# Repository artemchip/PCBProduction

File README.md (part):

## Домашняя фабрика прототипов печатных плат
Методов изготовления печатных плат очень много: сперва было ручное выцарапывание дорожек ножом, потом лак, потом лазерные принтеры и ЛУТ, потом фоторезист, и сейчас ЧПУ станки и фрезеровка дорожек.
Все методы делятся на травление и фрезеровку. Последняя недостаточна точна. Поэтому остановимся на первом. И в промышленности используется фоторезистивная его разновидность, а это явно не спроста.
Я расскажу как воспроизвести эти процессы в домашних условиях с точностью дорожка/зазор 0.1-0.15 мм, отверстие 0.2-0.3 мм, поясок 0.15 мм.

Да, на YouTube по запросу "изготовление печатных плат в домашних условиях" вы найдете много видео. Но мало где демонстрируется процесс металлизации отверстий, позволяющий изготавливать двухслойные платы. Да и все остальное там показывается плохо, недостаточно подробно, не учитываются нюансы и точные параметры процесса необходимые для достижения вышеуказанной околопромышленной точности и качества. Также там демонстрируются только удачные дубли, а весь брак, которого там 90% остается за кадром.

А что можно сказать про компании, которые занимаются изготовлением печатных плат на заказ, под ключ, профессионально? Если их спросить как они это успешно делают - то они ответят, что используют процесс, разработанный компанией X. А компания X предоставит вам базовую информацию, список этапов, но о тонкостях и параметрах каждого ничего не скажет, а лишь предложит за несколько миллионов рублей купить их оборудование которое делает каждый этап идеально. И даже если вы купите - вы не узнаете точный состав используемых растворов и иные параметры и будете зависеть от поставок этих растворов и иных материалов компанией X, ежегодно оплачивать дорогие лицензии их программного обеспечения, не говоря уже о том что оборудование рассчитано под большие панели и объемы и не подходит для прототипирования в плане стоимости и размеров.

Я представляю вам процесс в котором все используемое программное обеспечение разработано мной и имеет открытый исходный код, все используемые материалы доступны для свободного приобретения физическими лицами в малых объемах, все используемые растворы имеют открытый рецепт, точную инструкцию приготовления и каждый из ингредиентов - это не торговое название, а конкретная формула, все оборудование можно купить в любом месте, а не только у одной компании и его чертежи и 3D модели публично доступны.

## Точность

## Методы в фоторезистивной технологии
Ключевым моментом в изготовлении двухслойных плат является химическая металлизация стенок переходных отверстий.
Но их мало металлизировать, нужно их металлизацию защитить от растворения при травлении проводящего рисунка.
Поэтому существуют три метода такой защиты:
1. Тентинг-метод. Металлизацию отверстий защищает непосредственной сам пленочный фоторезист, за счет того что он толстый (50 мкм). Плюс данного метода в том, что он самый простой, легкий и дешевый. Минус - он неточный: дорожка/зазор 0.15 мм, отверстие 0.3 мм, поясок 0.2-0.3 мм. Самое главное - поясок отверстия должен быть большим.
2. Позитивный метод. Наиболее часто применяемый в промышленности. Фоторезист наносится на свободные от дорожек и отверстий участки, затем осаждается гальванический слой меди и поверх него той же гальваникой осаждается слой олова, либо олова-свинца. Плюс - точность выше: дорожка/зазор 0.1 мм, отверстие 0.2 мм, поясок 0.15 мм.
Минус - нужен дополнительный раствор для осаждения олова и удаления его. Также нужны оловяные электроды для его осаждения (которые дорогие). Этот раствор нестабилен, быстро разлагается, да и покрытие олова на медь имеет не очень хорошее сцепление, для решения этих проблем нужны проприетарные реактивы.
3. Полуаддитивный метод с дифференциальным травлением. Используется стеклотекстолит с тонкой медной фольгой (3 мкм). Выполняется осаждение меди на стенках отверстий, за счет чего усиливается и толщина основного слоя до 5 мкм. Фоторезист наносится на свободные от дорожек и отверстий участки, после чего толщина меди непокрытых им дорожках и отверстиях наращивается до 30-40 мкм той же гальваникой. Затем выполняется травление, 5 мкм стравливается быстро, а 40 мкм - не стравливается. Тут точность еще выше и дорожка/зазор может достигать 0.05 мм, но минус в том, что сложно найти на рынке стеклотекстолит FR-4 с такой тонкой фольгой. А брать 18 или 35 мкм и травить до толщины 3 мкм - неравномерно будет и ничего не получится. Стравить всю фольгу и затем с нуля осадить медь - недостаточно хорошо держаться будет.

В общем, надежно, стабильно и повторяемо в домашних условиях работает только первый метод. Он продемонстрирован в видео Demo.mp4 (Demo.zip).

## Тентинг-метод
1. Лист FR-4 и обработка на ЧПУ.
2. Химическое и гальваническое осаждение меди.
3. Нанесение фоторезиста, засветка, проявка.
4. Травление проводящего рисунка.
5. Удаление фоторезиста.
6. Нанесение паяльной маски, засветка, проявка, дубление.
7. Нанесение шелкографии.
8. Депанелизация.
9. Печать паяльной пасты, Pick & Place компонентов, пайка феном.

## Файлы проекта
Вам нужно экспортировать Gerber-файлы из САПР в котором вы разработали свою плату. Также если планируете сборку/пайку SMD нужно экспортировать centroid-файл.
Выбираем эти файлы в моем программном обеспечении, которое лежит в папке Software репозитория. Версия 3 более удобная и простая, версия 2 более расширенная.
С параметрами в главном меню лучше не играться. Если вы хотите панель побольше, чтобы уместить плату размером побольше или большее количество маленьких плат - вам придется переделывать файлы 3D моделей в последующих этапах, не исключены дополнительные проблемы.

## Лист FR-4 и обработка на ЧПУ
Я использую стеклотекстолит FR-4, листы 200x300 мм, толщина от 0.5 до 1.5 мм в зависимости от применения полученной печатной платы, толщина медной фольги от 18 мкм до 35 мкм. Продается много где.
Лучше использовать 18 мкм. Казалось бы, какая разница, 18 мкм или 35 мкм, но когда у вас дорожка/зазор 0.15 мм - разница существенная в боковом подтравливании.

Для обработки я использую ЧПУ станок CNC 3018 MAX с Aliexpress со шпинделем на 500 ватт.
После покупки станка я его доработал аппаратно:
1) добавил пылесборник на шпиндель, к которому подключаю пылесос (тоже продается на Aliexpress)
2) добавил камеру на каретку со шпинделем, 3D модели для печати крепления прилагаю
3) добавил микропереключатели чтобы сделать возможным homing

Важно откалибровать количество шагов на миллиметр у ЧПУ станка по каждой из осей, а также угол между осями XY и иные параметры. Делаю это один раз с помощью собственного программного обеспечения и фотошаблона, размещаемого в поле зрения камеры на рабочем поле станка.

Также нужно подобрать экспериментально скорость подачи и иные параметры.

В качестве подложки (жертвенного стола) я использую толстый (5 мм) лист FR-4 без фольги, на эту подложку уже креплю тонкий рабочий лист стеклотекстолита FR-4. Важно чтобы он ровно (без прогибов) ложился на подложку.
Выглядит и крепится это примерно так:

Я использую сверла фирмы X-CAN (с Ozon) для сверления основных и реперных отверстий и для вырезания квадратной панели фрезу 1.5 мм тоже от них. Выглядят они так:

Важно для сверления всех отверстий использовать сверла одной и той же фирмы из одной и той же серии, одной и той же длины, с одним и тем же хвостовиком чтобы они одинаково зажимались в патрон и сверление отверстий каждого диаметра происходило на одинаковом уровне оси Z и кривизна этой оси не портила позиционирование отверстий по XY. Также важно осторожно устанавливать сверло в патрон, не допуская изгиба, иначе центр вращения не совпадет с центром сверла и диаметр отверстия будет чуть больше.

Саму обработку тоже запускаю из своего программного обеспечения (как это делать показано в видео), важно подключать станок и его камеру в два USB порта (не использовать USB-хаб для объединения их в один), также не использовать USB-удлинители, потому что они могут неожиданно во время сверления оборвать соединение. Ранее я использовал Grbl Control, но там нет функционала повтора цикла, отметки какие отверстия просверлены, какие нет, превью, компенсация кривизны, т.е. функционал общий, не такой гибкий и заточенный под производство печатных плат, как в моем ПО.

Далее нужно снять заготовку с ЧПУ станка, обработать поверхность и края наждачкой зернистости от P400 до P800 (лучше последнее), не пропуская области вокруг отверстий (чтобы они тоже покрывались царапинами от зерен наждачки), проткнуть иголкой или сверлом каждое отверстие в котором застряла стружка, затем протереть безворсовой салфеткой, смоченной в изопропаноле и просушить 10 минут при 70C в конвекционной печи (пойдет обычная кулинарная, не микроволновая, а та что на ТЭНах).
Далее заготовку нужно взвесить, желательно с точностью до миллиграммов, чтобы в дальнейшем по плотности меди оценивать толщину фольги (но это необязательно).

При промывке изопропанолом необходимо использовать безворсовые салфетки (cleanroom wipers):

Вот так заготовка выглядит после этого этапа:

У меня заготовка около 122x122 мм, но вы можете в настройках программы попробовать установить другой размер, но вам придется и последующие этапы и станки под него адаптировать, и возможно вы наступите на грабли.
Не обязательно использовать CNC 3018 MAX, может подойти и другой ЧПУ станок. Но ручной микродрелью сверлить точно не стоит - отверстия будут неаккуратными и непригодными к следующему этапу. Да и в проводящий рисунок они не попадут. Даже с ЧПУ станком, но не откалиброванным не попадут, а вручную сверлить - шансов вообще нет. На YouTube у некоторых людей получается - но это везение и удачные попытки, повторяемость низкая, а неудачи остаются за кадром, да и неудобно это.

После этого этапа для перемещения заготовки нужно брать её за торцы (не за поверхность/середину). А если хочется положить заготовку, не делайте этого, ставьте вертикально на подставку.

От этого этапа до следующего можно её держать долго (хоть неделю).

В папке CNC лежат файлы настроек ПО под мой станок (они вам не сильно понадобятся, потому что у вас будут другие результаты калибровки), а также 3D модели (из Blender) деталей для печати из PETG пластика (адаптер для пылесборника, крепление для камеры, подставка и адаптер для депанелизации [о ней позже]).

Время этапа: около 30 минут.
Стоимость оборудования: $400.
Стоимость одного цикла: $1.5 (стоимость FR-4 + износ сверел и фрез).

## Химическое и гальваническое осаждение меди
Это очень важный этап в изготовлении двуслойных плат, поскольку соединяет два слоя путем осаждения меди на стенках отверстий. Не забываем про средства индивидуальной защиты от опасных веществ и о том, что подэтапы этой операции важно выполнять друг за другом и без пауз. Под паузой понимается перерыв дольше минуты-двух.
Моя установка выглядит так:

Что мы видим: рама, шаговый двигатель, ходовой винт и ездящий по одной оси стол. Это все взято и собрано из еще одного набора для сборки CNC 3018 (взял вариант на Ozon без шпинделя и лазера) и получил такой набор.
Этот стол движется туда-сюда для перемешивания всех ванн сразу. В моей программе можно нажать кнопку которая отправит необходимые для такого движения GCode команды, а можно сохранить их как файл. Также можно с его помощью сгенерировать файл GCode, залить на SD-карту и через автономный контроллер запускать его на этом станке, что я и делаю.

Перемешивать нужно именно в направлении которое показано на фото, т.е. поперек ванн, чтобы раствор затекал и смачивал отверстия в заготовке.
Не надо делать всякие другие механизмы перемешивания, они затратнее, опробованы мной и работают хуже.
На алюминиевом столе стоит полипропиленовый контейнер купленный в FixPrice. К его дну на "жидкие гвозди" приклеена подставка. В этих подставках стоят сами ванны.
Подставки напечатаны на 3D-принтере из PETG-пластика, файлы моделей прилагаю.

Также на крышке, которая держит заготовку, расположен соленоид. Он нужен чтобы бить в торец заготовки и вышибать из её отверстий диаметром 0.3 мм застрявшие пузырьки выделяющегося в процессе водорода.

Сами ванны напечатаны из чистого полипропилена (PP), конечно в YOUSU PP есть добавки которые снижают усадку и это хорошо, а в REC PP+ они еще лучше.
Полипропилен со стекловолокном (PP-GF) нельзя использовать, хоть он печатается легче, но он дает пористую структуру, у него спекаемость слоев и устойчивость к химии хуже, он будет протекать, спустя месяц раствор выльется из закрытой емкости и оставит налет. Не подойдут и другие 3D-печатные полимеры. Важна именно такая форма ванны, как в моих файлах 3D модели. Квадратная (прямоугольная) форма заставит медь оседать в углах сосуда и усложнит печать такой ванны, а также промывку после её использования.
Пластик PP сложный, необходим 3D принтер с закрытым объемом (пассивная или лучше активная термокамера). Я использовал Creality K1 Max, сопло 0.6 мм (не используйте 0.4 мм и менее, заклинит экструдер так как полипропилен мягкий).
Для обеспечения адгезии к столу необходимо положить лист полипропилена 4 мм (именно лист и именно такой толщины, можно больше, но не меньше). Важно его закрепить к столу зажимами, а лучше болтами.

Печатать нужно медленно 50 мм/сек при температуре 225C и без нагрева стола, с высотой слоя 0.1 мм.
Не печатайте на скотч, на специальные адгезивы и фирменные пленки для полипропилена, у вас ничего не получится, нужен именно лист (и толстый, 4-5 мм).
После печати вырезаем кусок из листа, печатаем подставку из PETG.
Приклеиваем дно ванны к дну подставки и ставим её в общее место. Пойдет любой каучуковый клей, хоть и пишут что для полипропилена он не подходит. А вот эпоксидный клей действительно тут не подходит. Вот так:

Печатаем также крышки из чистого PP, можно их подписать. Эти крышки плотно закрывают ванну обеспечивая герметичность и хранение растворов на месяцы и годы.
Также необходима рабочая крышка из PETG, с продетой в нее медной проволокой и зажимами крокодил, а также соленоидом, которые будут держать заготовку. Вот так:

Да, можно сделать лучше и чтоба она более ровно держала заготовку, но и так работает прекрасно.

Черные ванны у меня из ABS-GF4 с серыми крышками из PETG - они для воды, поэтому из таких простых пластиков.

Все ванны размещены в контейнере из того же полипропилена на всякий случай потому что может разлиться и пусть оно лучше туда выльется чем разольется по всему помещению.
3D печать из полипропилена - это лучший способ изготовить эту установку дома. Склеивание из листов, использование герметиков, других пластиков и методов не работает - герметики и клеи не устойчивы к химии и откажут после месяца работы, если конечно не сразу.
Литье может сработать, но в домашних условиях и единичном экземпляре - это весьма дорого.

В ваннах (справа налево) следующие растворы:
1. Кислая очистка.
2. Промывка 1.
3. Активация.
4. Пост-активация.
5. Промывка 2.
6. Химическое осаждение меди (electroless copper deposition).
7. Промывка 3.
8. Гальваническое осаждение меди (electrolytic copper deposition) (отдельно).

Состав этих растворов описан в Process 01.pdf лежащем тоже в репозитории. Только у меня 500 мл раствора, не как у Hydrogen Time, автора этой работы и соотвественно количество каждого ингредиента пропорционально больше. Главное готовить их на магнитной мешалке, не спешить и подождать подольше когда каждый ингредиент растворится перемешиванием почти полностью или вовсе полностью, перед добавлением следующего.
Для приготовления растворов используем дистилированную воду или даже деионизированную.
А вот для промывки можно фильтрованную питьевую из под крана, хотя лучше тоже дистилированную, особенно для промывки 2.
Раствор кислой очистки и активации условно вечный, живет год-два и больше, как понять, что он истек, написано в Process 01.pdf. Промывки меняю раз в 5-10 циклов производства. Пост-активатор меняю раз в 20-30 циклов. Химическую медь готовлю заново каждый цикл.
У меня кислая очистка, как и гальваническое осаждение меди (о котором позже) происходят при комнатной температуре, в отличии от Process 01.
Также там указано что раствор electroless copper deposition нужно после использования подкислять, и перед следующим использованием наоборот подщелачивать. Но не указано до какого pH, поэтому я просто в каждом производственном цикле готовлю его заново на магнитной мешалке непосредственно перед использованием. Тем более этот раствор склонен осаждать медь на любых пылинках, соринках, неровностях сосуда в который налит. Но если его использовать и после выливать и выбрасывать - проблем нет. Если после использования и слива раствора на его стенках все же осела медь - то желательно перед следующим циклом производства растворить её персульфатом аммония.
В составе electroless copper deposition не уточнено 4 капли Тритон X-100 - это сколько. Я использую 0.1-0.15 мл на 500 мл раствора (отмеряю шприцом).

Также рецепт раствора electrolytic copper deposition у меня другой (живет около 1 цикла производства, если заготовка 122x122 мм и ванна 2л):
750 мл дистилированной воды (горячей, 80C)
180 г медного купороса
130 мл серной кислоты (45% аккумуляторной 1.28 г/см^2)
0,06 г тиомочевины
0,06 г хлорида натрия
0.05-0.1 мл Тритон X-100
Долить воды до отметки в 1 литр

Можно использовать вариант с проприетарным блескообразователем (живет около 4 циклов производства, если заготовка 122x122 мм и ванна 2л):
750 мл дистилированной воды (горячей, 80C)
160 г медного купороса
200 мл серной кислоты (45% аккумуляторной 1.28 г/см^2)
0.07 г хлорида натрия
5 мл Купралайт-7400
Долить воды до отметки в 1 литр

Есть еще рецепт от канала "шоу бородатого инженера" (не проверял, не знаю насколько хорошо работает):
750 мл дистилированной воды (горячей, 80C)
250 г медного купороса
200 г серной кислоты (45% аккумуляторной 1.28 г/см^2)
5 мг тиомочевины
2,7-нафталиндисульфокислота 0.5г/л
Возможно несколько капель Тритон X-100 или иного ПАВ
Долить воды до отметки в 1 литр

После истечения "срока жизни" покрытие неравномерное. Вы можете следить за истечением его срока службы по уровню мутности раствора, он возрастет когда срок начнет подходить к концу.

Этот раствор заливается вот в такую ванну из полипропиленового контейнера (3D модели тоже прилагаю). Тут шаговый двигатель, который перемешивает раствор покачиванием заготовки на 5-10 мм по нижнему краю.
Вот как это выглядит:

Электроды - это шины из меди М1 размером 3 х 30 х 200 мм, обернутые в полипропиленовую химостойкую ткань (анодные чехлы), для защиты от образования шлама. Конечно лучше медь с добавлением фосфора, но у меня без.
Они должны иметь именно такой размер и площадь и располагаться по обе стороны заготовки, иначе покрытие будет неравномерным. Суммарная площадь анодов должна быть вдвое больше площади заготовки. И они должны для большей равномерности быть подальше от неё. Они будут растворяться в процессе работы, аноды такого размера растворятся наполовину лишь после 100 циклов производства, после их нужно заменить. Каждые 5 циклов производства необходимо отмывать аноды от шлама (промывать чехол водой и обрабатывать сам медный анод наждачкой).

В Process 01 также указан порядок действий для тентинг-метода: clean, water rinse, activate, post activate, water rinse, electroless copper, water rinse, electrolytic copper, water rinse.
Но у меня время другое: clean - 10 минут, activate - 10 минут, post-activate - 5 минут, electroless copper - 1 час, electrolytic copper - 1 час 10 минут.
"Water rinse" в Process 01 - это я просто опускаю заготовку (вместе с крышкой на которой она закреплена) в ванну промывки, на время от 2 до 5 секунд.

Если в растворе активатора плавают хлопья - нужно их отфильтровать, если не помогло - значит истек его срок годности и нужно его приготовить заново.

Итак, выполняем микротравление в горячем (60C) 20% растворе персульфата аммония 10-20 секунд (ну или не очень микро если у нас 35 мкм FR-4, чтобы оставить 18 мкм, 2-3 минуты), затем промываем водой, затем обрабатываем в 5% растворе гидроксида натрия (2 минуты), промываем водой, далее поочередно опускаем заготовку в каждую из ванн системы на нужное время.
Поправка: в видео показана обработка в растворе гидроксида натрия, но вместо этого нужно обрабатывать в 20% растворе лимонной кислоты, как показал опыт после съемки видео.

После химического осаждения меди (electroless copper deposition) проверьте края (торцы) заготовки, если они полностью покрыты медью - подэтап удался, если нет - промойте заготовку водой, повторите активацию, пост-активацию, промывку и выполните химическое осаждение заново в новом растворе химической меди. Если и это не помогло, приготовьте заново растворы активатора и пост-активатора.

Если все нормально - то промываем водой (аккуратно, погружением, можно двойным, чтобы отмыть полностью) и в последнюю ванну [electrolytic copper deposition] погружаем с постоянным током около 2 А на заготовку 122x122 мм (если у вас больше/меньше - пересчитайте пропорционально), заготовка к минусу, аноды к плюсу. Раствор я держу при комнатной температуре, не нагревая его до 60C как Hydrogen Time. Важно как можно больше соединений проводов с заготовкой и анодами сделать паянными, чтобы не болтались.

Если после этого процесса появляются сильные неровности, наросты и большие кристаллы меди, а также сильные заусенцы на углах - значит сила тока слишком большая или электролит грязный, нужно готовить раствор заново и повторять все сначала.

Если все получилось равномерно - промываем водой (хоть из под крана), сушим в печи при 70C около 10 минут и обрабатываем наждачкой Р800, промывая изопропанолом и протирая безворсовыми салфетками. Ставим заготовку на подставку. И так она может дожидаться следующего этапа до нескольких часов точно. Но при дальнейшем её перемещении берите её пальцами за торцы и технологические поля, а вообще в идеале еще и в перчатках.

Результат:

Вы можете взвешивать заготовку до, во время и после процесса, чтобы по массе через плотность меди вычислить толщину (сколько осадили). Только взвешивайте предварительно просушив.

Если вы оставляете этот раствор [electrolytic copper deposition] стоять более 10 минут в ванне без тока и перемешивания - вынимайте из неё аноды и заготовку.

Не используйте всякие графитовые спреи/углеродные краски которые советуют для создания проводимости перед гальваникой самоделкины, это ненадежно. Также ненадежно использование термореактивных веществ типа аммиачного комплекса гипофосфита меди. Если даже оно будет работать устойчиво - то большие (3-5 мм) отверстия непрокроются, и стенки будут не всегда ровные, и еще большой вопрос не сломается ли такая плата в процессе эксплуатации.

Не используйте механическую металлизацию (гильзование), она трудоемка и не выдерживает процесс reflow soldering, да и размеры via там большие.

В папке Galvo есть blend-файл с 3D моделями всего вышеупомянутого.

Время этапа: чуть меньше 2 часов.
Стоимость оборудования: $500 (реактивы, пластик для ванн, механизмы перемешивания, лабораторная посуда, установки вакуумной фильтрации, медные аноды).
Стоимость одного цикла: $0.1 (в случае с электролитом на основе Купралайт-7400), $2 (в случае с моим рецептом).

## Фоторезист: нанесение, засветка, проявка
Ну во-первых: он бывает пленочный и жидкий.
Жидкий редко где встретишь, аэрозольные балоны Kontakt Chemie Positiv 20 и Cramolin Positiv Resist дорогие и мало где продаются, также есть жидкий в банках, содержимое их нужно растворять в этилацетате и распылять с помощью аэрографа.
Ну, во-первых вы не сможете руками распылять одинаково толстый слой при каждом цикле производства, а от толщины зависит энергия экспонирования (сколько света должно попасть). Если конечно не закрепите аэрозольный баллон на каретке ЧПУ станка, который впоследствии испачкается этой жидкостью. Помимо этого, жидкий воняет, к нему прилипает пыль, его нужно 15 минут сушить в конвекционной печи. Да и он как правило позитивный, т.е. те участки куда попал свет растворяются. Это значит что при травлении придется держать свет выключенным, об этом позже.
Да и полезных свойств у жидкого фоторезиста нет: он неспособен как пленка, закрывать собой (образовывать крышки) на отверстиях - следовательно не годится для тентинг метода, а еще не все марки и модели устойчивы в кислых гальванических ваннах, что делает его непригодным для двух оставшихся методов. Да также он слишком тонкий для них. Пригоден он только для однослойных плат.

Промышленность использует пленочный. Я использую Laminar E7715 и Aqua Mer ME720 толщиной 38 мкм. Вы можете использовать любой толщиной от 30 до 50 мкм, годящийся согласно datasheet для тентинг метода. Главное покупайте его у надежного поставщика, храните в темноте, убеждайтесь при покупке, что светозащитная упаковка не вскрыта и на пленке не должно быть царапин, ляпов, полос, волн, ряби и иных дефектов:  
  
Вы их можете даже после проявки не увидеть, а вот при травлении они вам все испортят из-за недостаточной адгезии в этих местах.

Перед нанесением фоторезиста очень важно подготовить поверхность. Да, грубые техпроцессы могут и без такового получится, но если дорожка/зазор 0.1-0.15 мм - это обязательно.
Для этого нужно (обязательно):
1. Обработать наждачкой P600-P800, промыть изопропанолом и протереть безворсовыми салфетками.
2. Микротравление (10-20 секунд в холодном (15C) 20% растворе персульфата аммония), промыть водой.
3. Обработать в 3-5% растворе гидроксида натрия (нет, в 20% растворе лимонной кислоты как показал опыт полученный после съемки видео) в течение 2-5 минут, промыть водой.
Вот как будет если обработать гидроксидом натрия:
    
А вот как если в лимонной кислоте (на дефекты маски внимания не обращать, не нашел качественного поставщика):
    
4. Просушить в печи при 80C 5-10 минут до полной сухости. Вы можете за неиспользуемые технологические поля с краев потрогать заготовку - она должна на ощупь "скрипеть", быть такой же как посуда после тщательного мытья.
5. Проверить рисунок (экспортировать его из моей программы кнопкой "сохранить" в разделе "засветка фоторезиста" и сравнить с тем, что показывает ваш САПР). Экспортированные из Autodesk EAGLE изредка она воспринимает не так. В случае отличий, в их местах удалить дорожку и создать её заново, пере-экспортировать и снова сравнить, и так пока отличия не исчезнут.

Итак, выключаем свет. Чтобы что-то видеть нужно использовать красный или желтый осветительной прибор (это должен именно светодиод этих конкретных цветов, монохроматический, одной длины волны, около 600 нм, не RGB [выше 550 нм фоторезист не чувствителен]).
Достаем рулон, отрезаем нужный кусок. Отрезать квадрат на 1 см больше заготовки (или меньше, см. примечание ниже). Отрезаем 2 штуки (на каждую из сторон). Я использую для этого резак для бумаги, но вы можете и ножницами:

Важно убедиться, что на поверхности фоторезиста нет ряби, в противном случае это брак или у него истек срок годности (бывает, что и такое продают).

Берем лист бумаги A4. Сгибаем пополам, раскрываем, кладем рядом со входом ламинатора, сгибом к нему. С куска фоторезиста снимаем защитную пленку (на более шероховатой стороне), с помощью куска скотча или двух кусков скотча.
Эта пленка должна отдираться плавно (не рывками). Кладем на лист бумаги лист фоторезиста, затем заготовку (остывшую хотя бы до 30C после сушки), затем лист фоторезиста (липкой/шероховатой стороной с которой сняли пленку к заготовке). Посмотрите на мои движения в видео и точно повторяйте их. С другой стороны заготовки тоже самое.
Ну а если не можете лучше возьмите рулонный ламинатор который подороже.
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
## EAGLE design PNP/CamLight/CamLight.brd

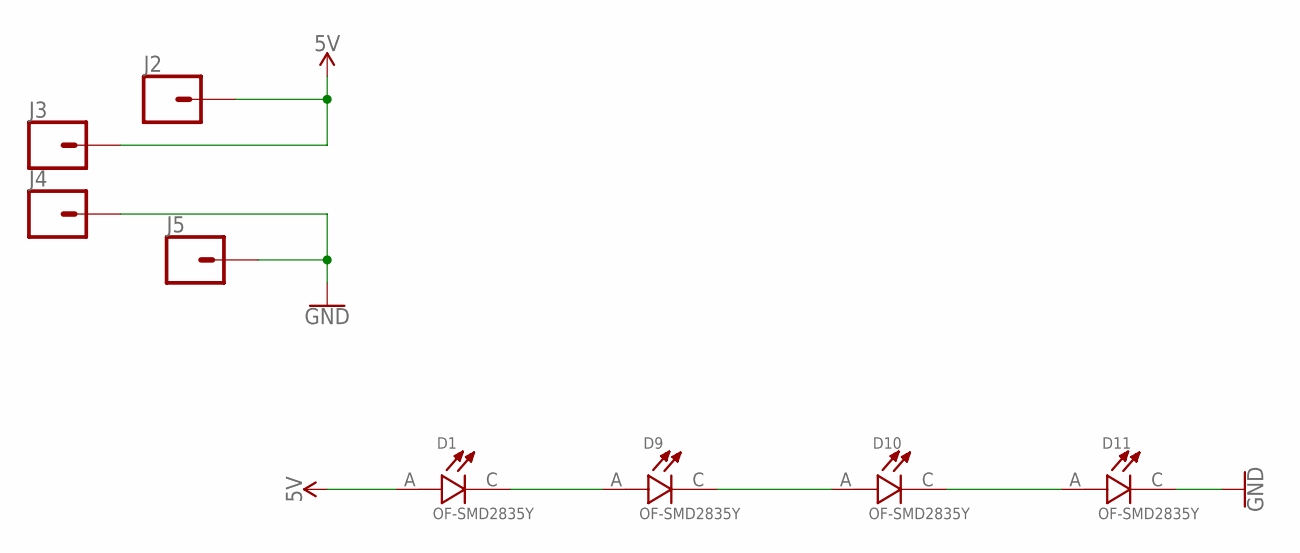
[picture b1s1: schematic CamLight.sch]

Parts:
D1, D9, D10, D11: OF-SMD2835Y; LED_OF-SMD2835Y
J2, J3, J4, J5: CONN_01; 1X01

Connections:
5V: D1.A, J2.1, J3.1
GND: D11.C, J4.1, J5.1
unnamed: D10.C, D11.A
unnamed: D9.C, D10.A
unnamed: D1.C, D9.A

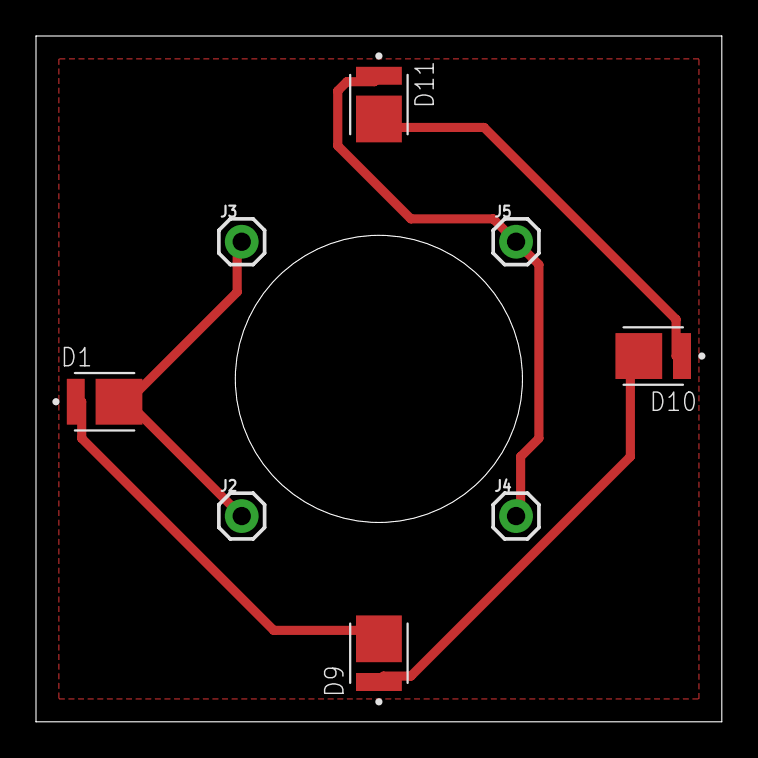
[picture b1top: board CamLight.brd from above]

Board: 2 copper layers, 38.1 x 38.1 mm, 8 parts (0 on the bottom side), 5 nets.

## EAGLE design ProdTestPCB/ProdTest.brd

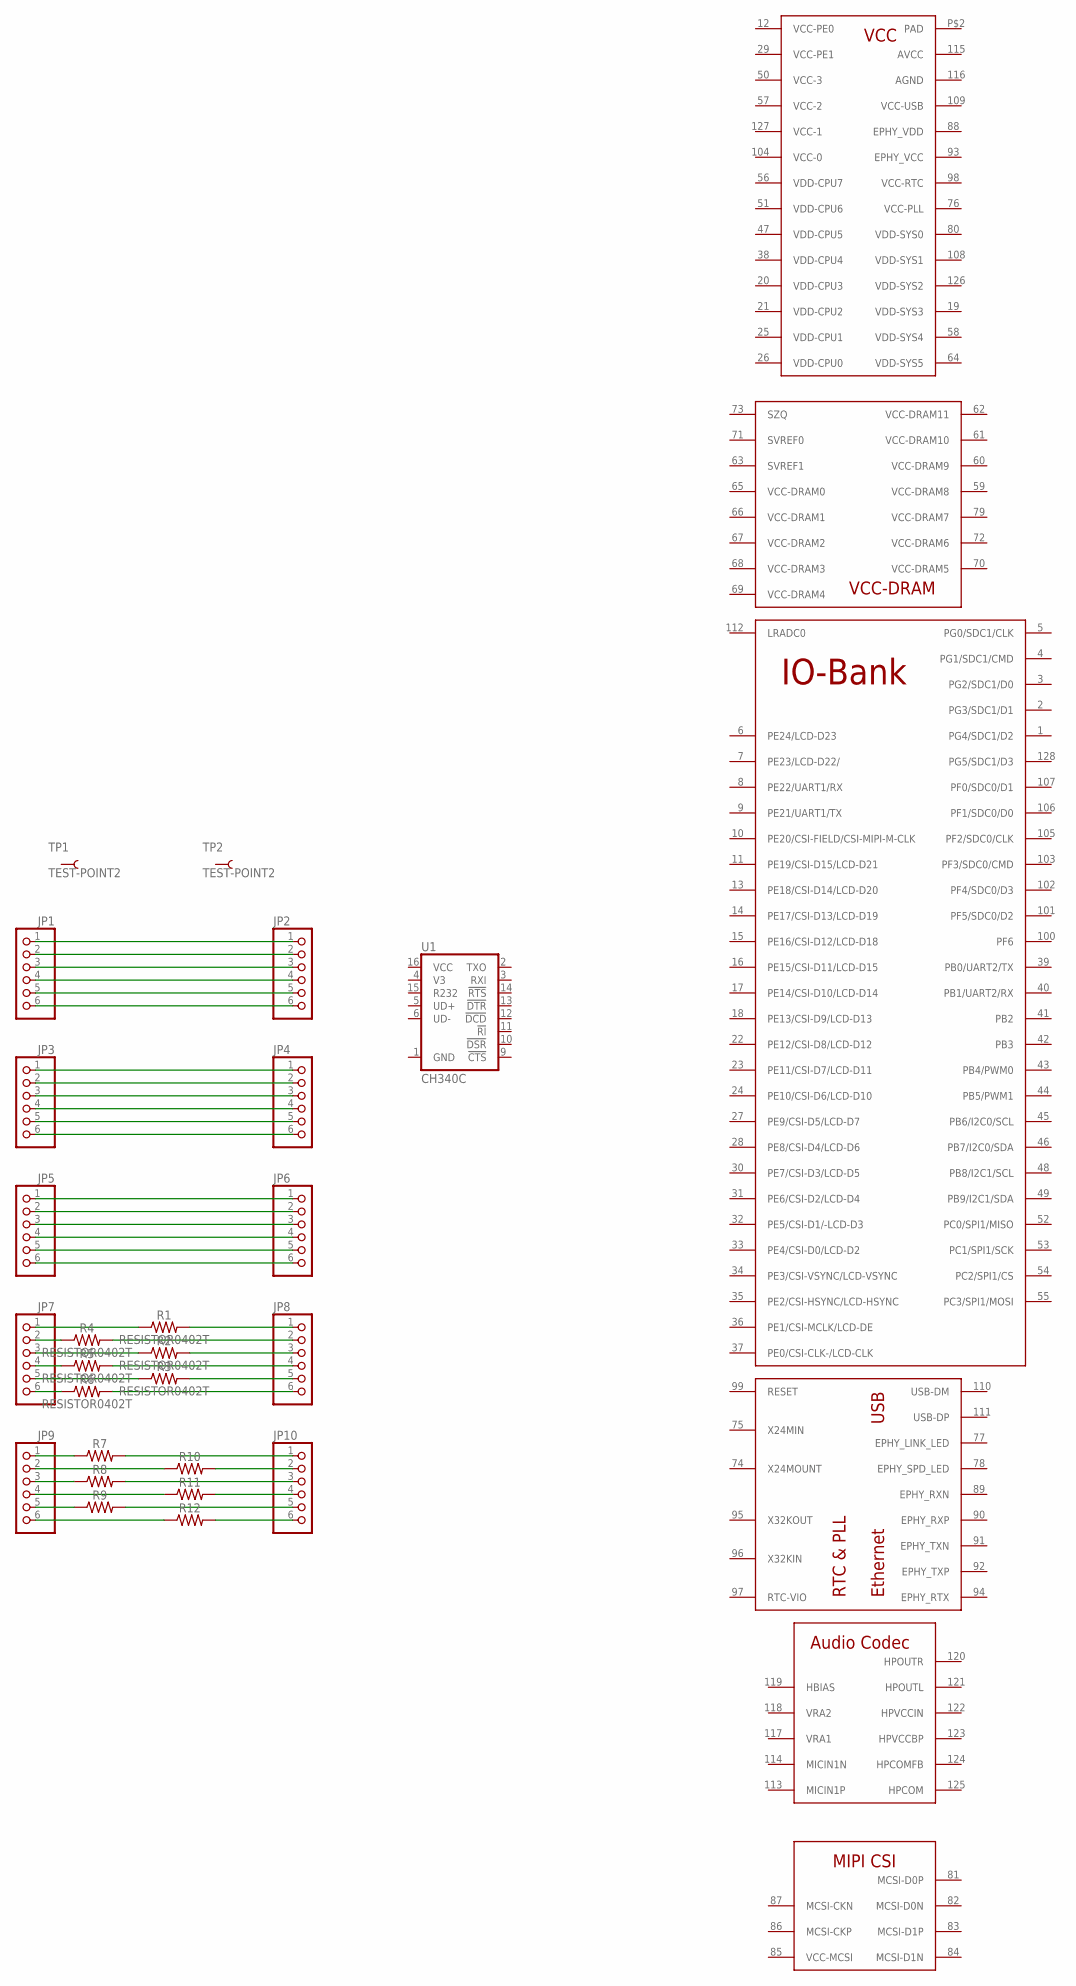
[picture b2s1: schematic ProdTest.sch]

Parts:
JP1, JP2, JP3, JP4, JP5, JP6, JP7, JP8, JP9, JP10: PINHD-1X6; 1X06
R1, R2, R3, R4, R5, R6: RESISTOR0402T; 0402-TIGHT
R7, R8, R9, R10, R11, R12: 0603
TP1, TP2: TEST-POINT2; PAD.02X.02
U1: CH340C; SO016
U$1: V3S; QFP-128

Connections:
unnamed: JP1.1, JP2.1
unnamed: JP1.2, JP2.2
unnamed: JP1.3, JP2.3
unnamed: JP1.4, JP2.4
unnamed: JP1.5, JP2.5
unnamed: JP1.6, JP2.6
unnamed: JP3.1, JP4.1
unnamed: JP3.2, JP4.2
unnamed: JP3.3, JP4.3
unnamed: JP3.4, JP4.4
unnamed: JP3.5, JP4.5
unnamed: JP3.6, JP4.6
unnamed: JP5.1, JP6.1
unnamed: JP5.2, JP6.2
unnamed: JP5.3, JP6.3
unnamed: JP5.4, JP6.4
unnamed: JP5.5, JP6.5
unnamed: JP5.6, JP6.6
unnamed: JP9.1, R7.1
unnamed: JP9.2, R10.1
unnamed: JP9.3, R8.1
unnamed: JP9.4, R11.1
unnamed: JP9.5, R9.1
unnamed: JP9.6, R12.1
unnamed: JP10.5, R9.2
unnamed: JP10.6, R12.2
unnamed: JP10.4, R11.2
unnamed: JP10.2, R10.2
unnamed: JP10.1, R7.2
unnamed: JP10.3, R8.2
unnamed: JP7.2, R4.1
unnamed: JP7.4, R5.1
unnamed: JP7.6, R6.1
unnamed: JP7.5, R3.1
unnamed: JP7.3, R2.1
unnamed: JP7.1, R1.1
unnamed: JP8.2, R4.2
unnamed: JP8.1, R1.2
unnamed: JP8.3, R2.2
unnamed: JP8.4, R5.2
unnamed: JP8.5, R3.2
unnamed: JP8.6, R6.2

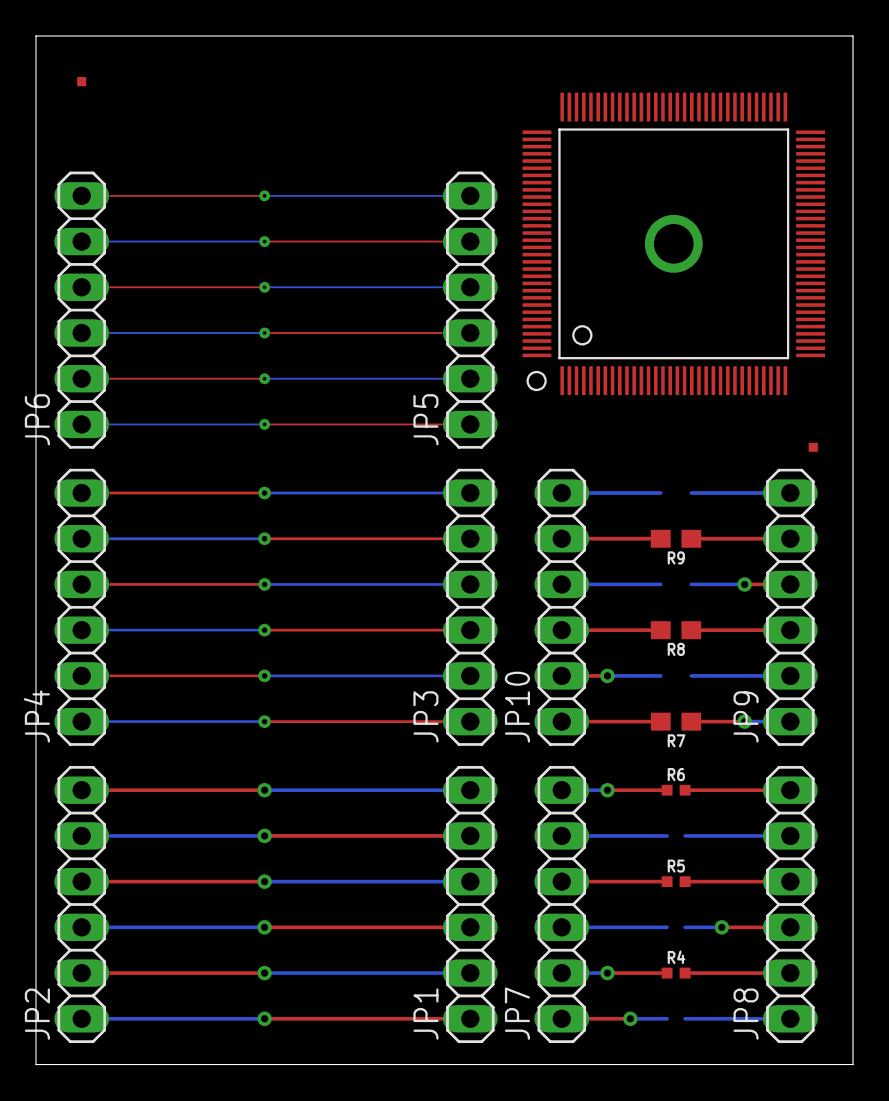
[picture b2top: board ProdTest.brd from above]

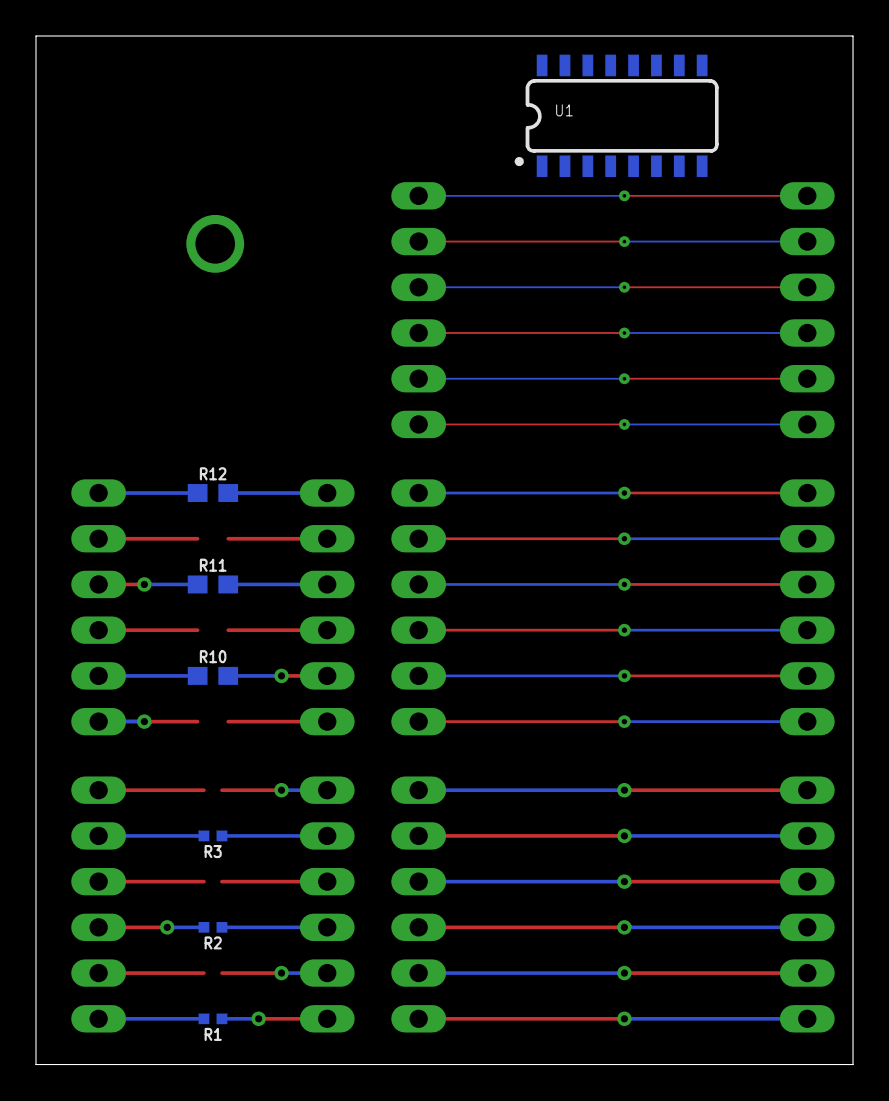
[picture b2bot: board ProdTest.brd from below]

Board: 2 copper layers, 45.4 x 57.1 mm, 26 parts (7 on the bottom side), 42 nets.

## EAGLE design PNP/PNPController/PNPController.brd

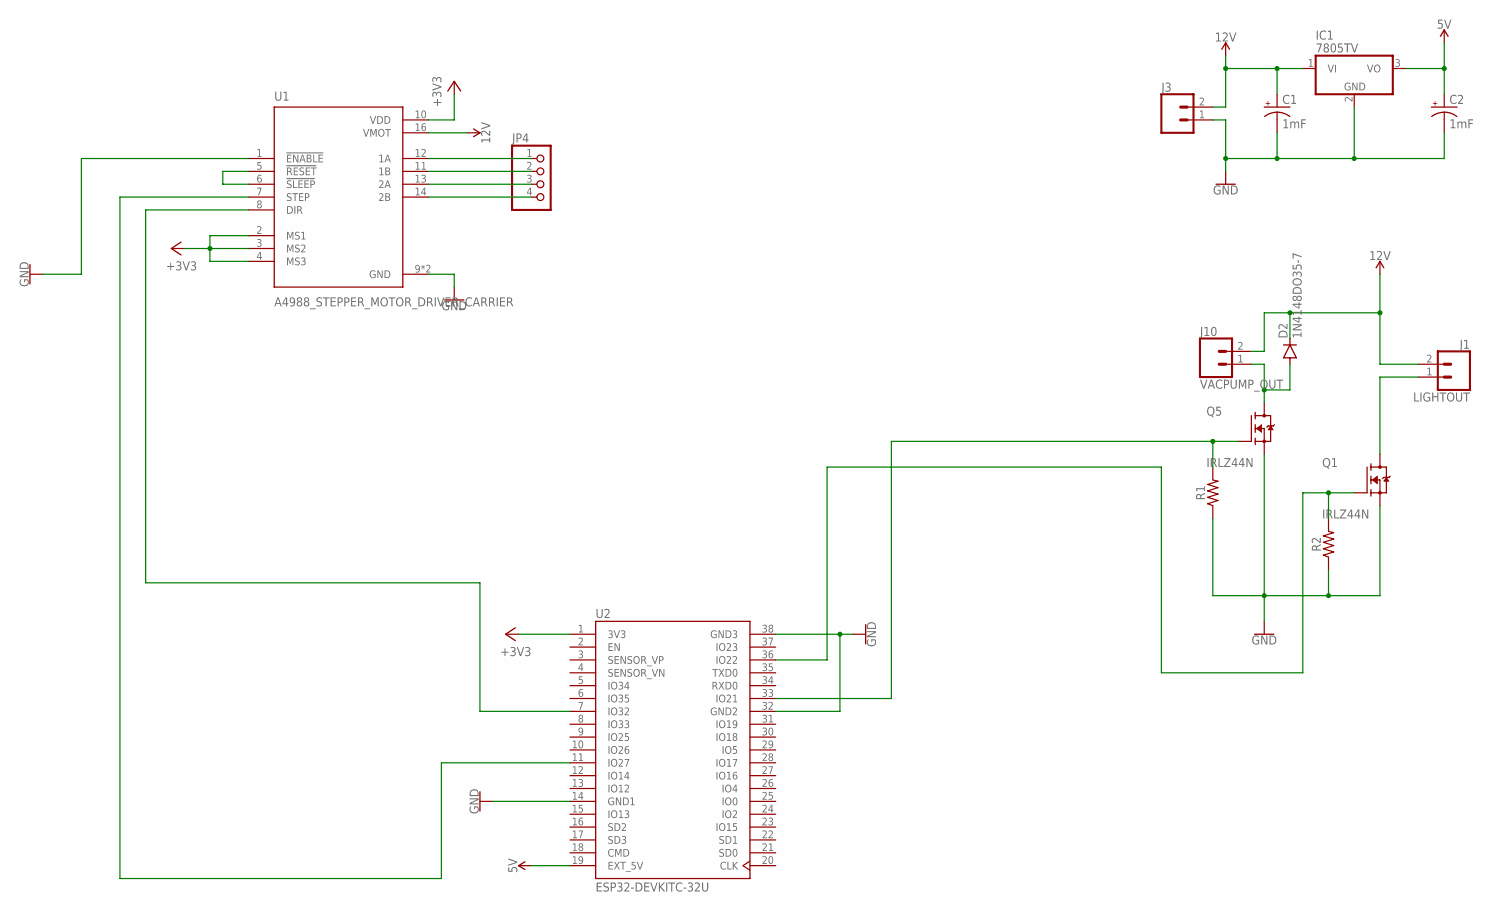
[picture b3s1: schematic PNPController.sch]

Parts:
C1, C2: 1mF; CPOL-RADIAL-5MM-10MM
D2: 1N4148DO35-7; DO35-7
IC1: 7805TV; TO220V
J1: LIGHTOUT; SCREWTERMINAL-3.5MM-2
J3: CONN_025MM; SCREWTERMINAL-5MM-2
J10: VACPUMP_OUT; SCREWTERMINAL-3.5MM-2
JP4: PINHD-1X4; 1X04
Q1, Q5: IRLZ44N; TO254P1054X469X1930-3
R1, R2: AXIAL-0.3
U1: A4988_STEPPER_MOTOR_DRIVER_CARRIER; MODULE_A4988_STEPPER_MOTOR_DRIVER_CARRIER
U2: ESP32-DEVKITC-32U; MODULE_ESP32-DEVKITC-32U

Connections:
5V: C2.+, IC1.3 (VO), U2.19 (EXT_5V)
12V: C1.+, D2.C, IC1.1 (VI), J1.2, J3.2, J10.2, U1.16 (VMOT)
+3V3: U1.2 (MS1), U1.3 (MS2), U1.4 (MS3), U1.10 (VDD), U2.1 (3V3)
GND: C1.-, C2.-, IC1.2 (GND), J3.1, Q1.3 (S), Q5.3 (S), R1.P$1 (1), R2.P$1 (1), U1.1 (!ENABLE), U1.9 (GND), U1.15 (GND), U2.14 (GND1), U2.32 (GND2), U2.38 (GND3)
unnamed: JP4.1, U1.12 (1A)
unnamed: JP4.2, U1.11 (1B)
unnamed: JP4.3, U1.13 (2A)
unnamed: JP4.4, U1.14 (2B)
unnamed: U1.5 (!RESET), U1.6 (!SLEEP)
unnamed: D2.A, J10.1, Q5.2 (D)
unnamed: J1.1, Q1.2 (D)
unnamed: Q5.1 (G), R1.P$2 (2), U2.33 (IO21)
unnamed: Q1.1 (G), R2.P$2 (2), U2.36 (IO22)
unnamed: U1.7 (STEP), U2.11 (IO27)
unnamed: U1.8 (DIR), U2.7 (IO32)

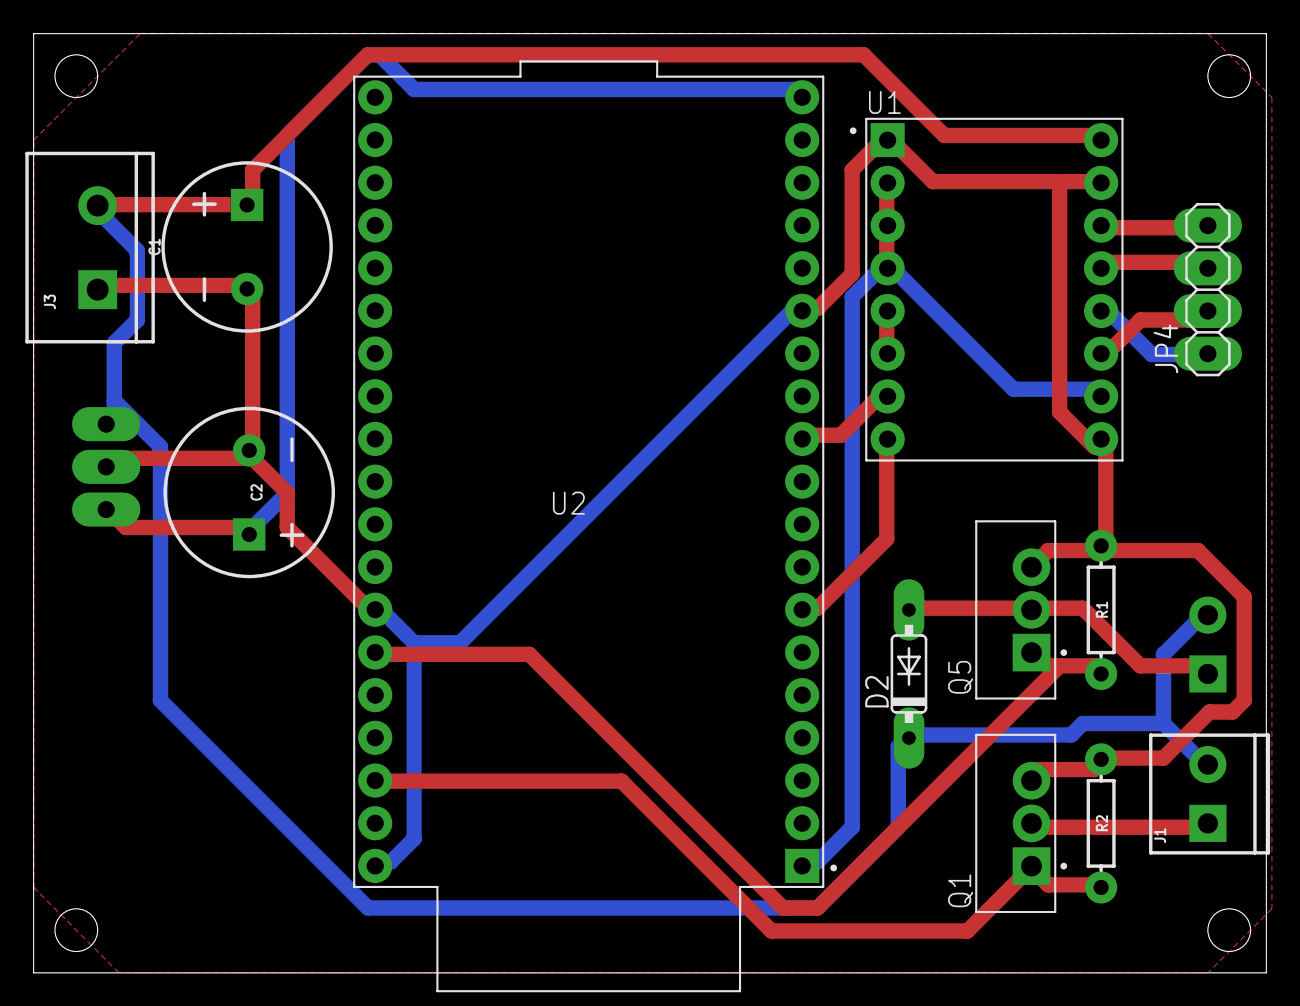
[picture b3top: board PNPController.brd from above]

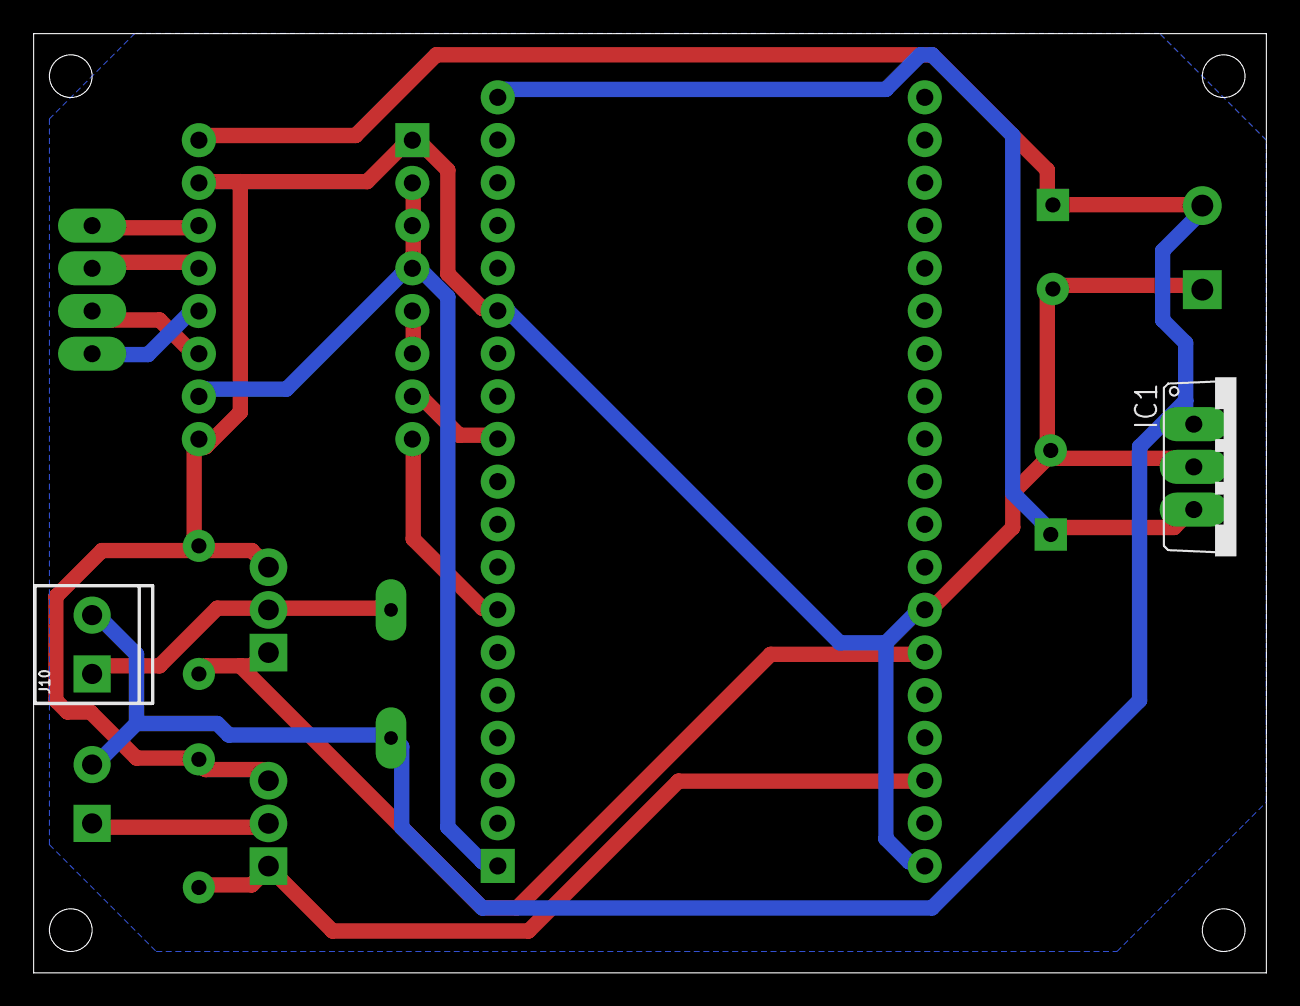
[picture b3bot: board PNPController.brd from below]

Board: 2 copper layers, 73.3 x 55.9 mm, 14 parts (2 on the bottom side), 15 nets.

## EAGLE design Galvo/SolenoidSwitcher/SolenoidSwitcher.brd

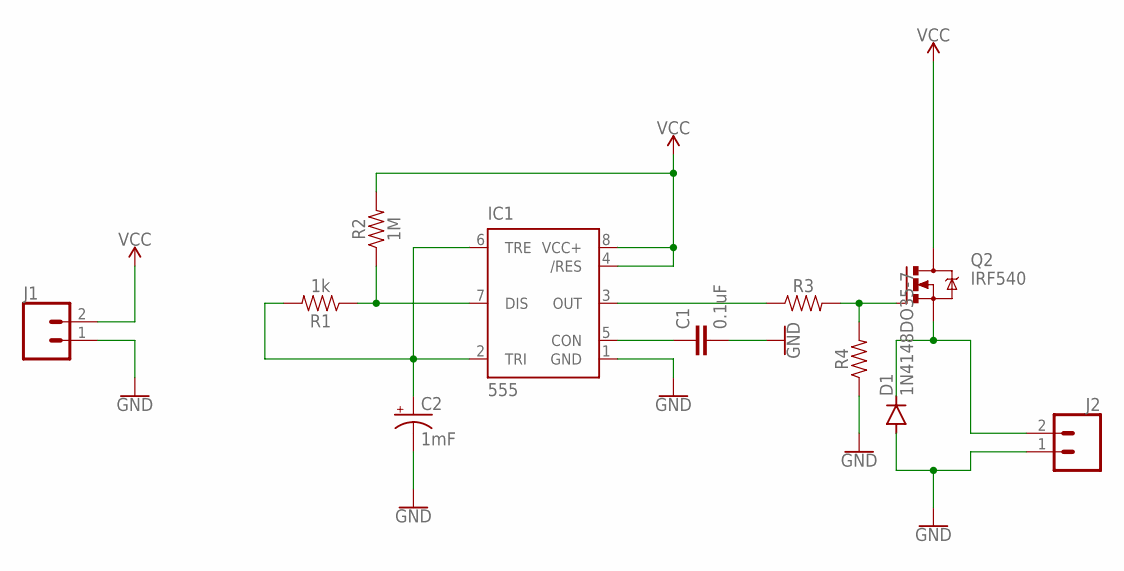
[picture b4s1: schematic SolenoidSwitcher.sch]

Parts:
C1: 0.1uF; CAP-PTH-SMALL-KIT
C2: 1mF; CPOL-RADIAL-5MM-10MM
D1: 1N4148DO35-7; DO35-7
IC1: 555; DIP08
J1, J2: CONN_02; 1X02
Q2: IRF540; TO220BV
R1: 1k; AXIAL-0.1
R2: 1M; AXIAL-0.1
R3, R4: AXIAL-0.3

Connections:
GND: C1.2, C2.-, D1.A, IC1.1 (GND), J1.1, J2.1, R4.P$1 (1)
unnamed: IC1.3 (OUT), R3.P$1 (1)
unnamed: C2.+, IC1.2 (TRI), IC1.6 (TRE), R1.P$2 (2)
unnamed: Q2.G, R3.P$2 (2), R4.P$2 (2)
unnamed: C1.1, IC1.5 (CON)
unnamed: IC1.7 (DIS), R1.P$1 (1), R2.P$1 (1)
unnamed: D1.C, J2.2, Q2.S
VCC: IC1.4 (/RES), IC1.8 (VCC+), J1.2, Q2.D, R2.P$2 (2)

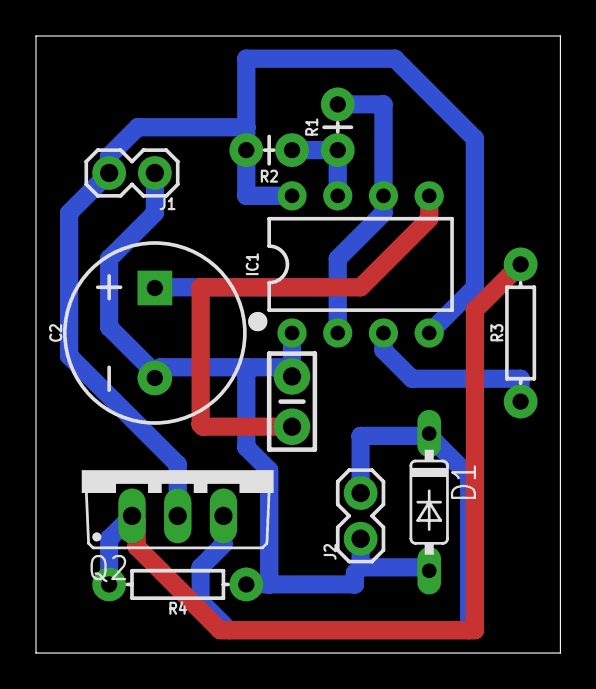
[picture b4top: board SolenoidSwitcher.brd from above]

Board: 2 copper layers, 29.1 x 34.3 mm, 11 parts (0 on the bottom side), 8 nets.

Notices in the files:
parts and their libraries:
SparkFun-Capacitors: Licensing: Creative Commons ShareAlike 4.0 International - https://creativecommons.org/licenses/by-sa/4.0
